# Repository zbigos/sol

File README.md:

# sol
high power LED lamp for workshop use

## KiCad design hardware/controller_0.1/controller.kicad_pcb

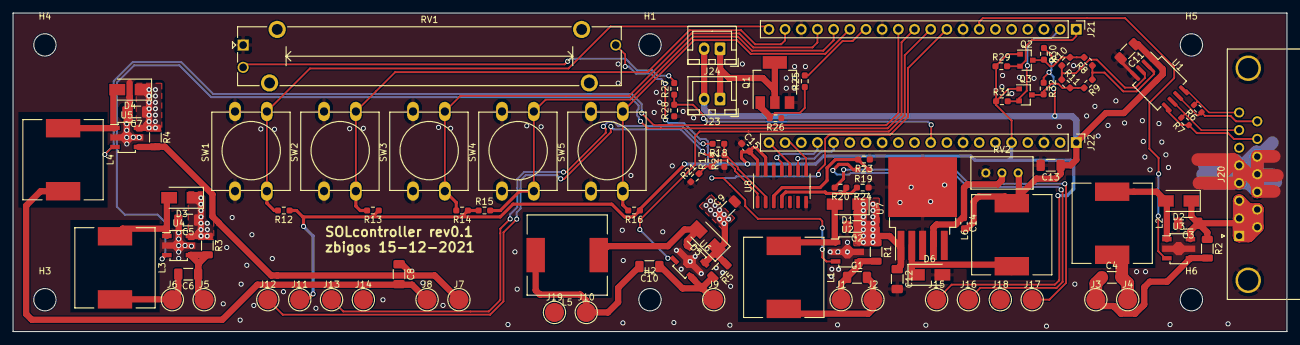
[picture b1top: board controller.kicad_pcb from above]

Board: 2 copper layers, 200.0 x 50.0 mm, 107 parts (0 on the bottom side), 58 nets.

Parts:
C1, C2, C3, C4, C5, C6, C7, C8, C9, C10, C11, C12, C13: C_Small; C_1206_3216Metric_Pad1.33x1.80mm_HandSolder
C14, C15: C_Small; C_0603_1608Metric_Pad1.08x0.95mm_HandSolder
D1, D2, D3, D4, D5, D6: D_Schottky; D_SMA
H1, H2, H3, H4, H5, H6: MountingHole; MountingHole_3.5mm
J1, J2, J3, J4, J5, J6, J7, J8, J9, J10, J11, J12, J13, J14, J15, J16, J17, J18, J19: Conn_01x01; TestPoint_Pad_D3.0mm
J20: DB15_Male_MountingHoles; DSUB-15_Male_Horizontal_P2.77x2.84mm_EdgePinOffset9.90mm_Ho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
J21, J22: Conn_01x20; PinHeader_1x20_P2.54mm_Vertical
J23, J24: Conn_01x02; JST_XH_B2B-XH-A_1x02_P2.50mm_Vertical
L1, L2, L3, L4, L5, L6: INDUCTOR; L_12x12mm_H8mm
Q1: Q_NMOS_GDS; SOT-223-3_TabPin2
Q2, Q3: BSS138; SOT-23
R1, R2, R3, R4, R5: R; R_1206_3216Metric
R6, R7: R_Small; R_0603_1608Metric
R8, R9, R10, R11, R12, R13, R14, R15, R16, R17, R18, R19, R20, R21, R22, R23, R24, R25, R26, R27, R28, R29, R30, R31, R32: R_Small; R_0603_1608Metric_Pad0.98x0.95mm_HandSolder
RV1: R_POT; Potentiometer_Bourns_PTA4543_Single_Slide
RV2: R_POT; Potentiometer_Bourns_3296W_Vertical
SW1, SW2, SW3, SW4, SW5: SW_Push; SW_PUSH-12mm
U1: MAX490E; SO-8_5.3x6.2mm_P1.27mm
U2, U3, U4, U5, U6: SCT2932F; SOT-89-5
U7: LM2596S-ADJ; TO-263-5_TabPin3
U8: MCP3204; SOIC-14_3.9x8.7mm_P1.27mm

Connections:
+5V: C11.1, C13.1, C14.2, J22.1, J23.2, J24.2, L6.2, R30.1, R32.1, RV2.1, U1.1 (VCC)
/3V3pico: C15.2, J11.1, J15.1, J22.5, Q2.1 (G), Q3.1 (G), R12.1, R13.1, R14.1, R15.1, R16.1, R29.1, R31.1, RV1.3, U8.13 (Vref), U8.14 (Vdd)
/B1: J21.20, R12.2, SW1.2
/B2: J21.19, R13.2, SW2.2
/B3: J21.17, R14.2, SW3.2
/B4: J21.16, R15.2, SW4.2
/B5: J21.15, R16.2, SW5.2
/CH1_CONTROL: J21.9, U2.3 (DIM)
/CH1_SINK: C1.2, J2.1, L1.2
/CH1_VSUP: C1.1, J1.1, R1.2, U2.4 (Isense)
/CH2_CONTROL: J21.7, U3.3 (DIM)
/CH2_SINK: C4.2, J4.1, L2.2
/CH2_VSUP: C4.1, J3.1, R2.2, U3.4 (Isense)
/CH3_CONTROL: J21.11, U4.3 (DIM)
/CH3_SINK: C6.2, J6.1, L3.2
/CH3_VSUP: C6.1, J5.1, R3.2, U4.4 (Isense)
/CH4_CONTROL: J21.12, U5.3 (DIM)
/CH4_SINK: C8.2, J8.1, L4.2
/CH4_VSUP: C8.1, J7.1, R4.2, U5.4 (Isense)
/CH5_CONTROL: J21.10, U6.3 (DIM)
/CH5_SINK: C10.2, J10.1, L5.2
/CH5_VSUP: C10.1, J9.1, R5.2, U6.4 (Isense)
/CLK: J22.17, U8.11 (CLK)
/FANCONTROL: J21.14, R25.2
/HRSRx: Q3.3 (D), R9.2, R11.2, R32.2
/HRSTx: Q2.3 (D), R8.2, R10.2, R30.2
/LEDRAIL: C2.1, C3.1, C5.1, C7.1, C9.1, C12.1, D1.1 (K), D2.1 (K), D3.1 (K), D4.1 (K), D5.1 (K), J20.1, J20.2, J20.3, J20.9, J20.10, R1.1, R2.1, R3.1, R4.1, R5.1, U2.5 (VIN), U3.5 (VIN), U4.5 (VIN), U5.5 (VIN), U6.5 (VIN), U7.1 (VIN)
/MISO: J22.20, U8.10 (Dout)
/MOSI: J22.16, U8.9 (Din)
/POT: J22.10, R27.1, R28.2
/RSRx: J21.2, Q3.2 (S), R31.2
/RSTx: J21.1, Q2.2 (S), R29.2
/TCHANNEL_1: J12.1, R17.2
/TCHANNEL_2: J13.1, R18.2
/TCHANNEL_3: J16.1, R19.2
/TCHANNEL_4: J17.1, R20.2
/nCS: J22.19, U8.8 (~CS~/SHDN)
GND: C2.2, C3.2, C5.2, C7.2, C9.2, C11.2, C12.2, C13.2, C15.1, D6.2 (A), J14.1, J18.1, J19.1, J20.0 (PAD), J20.4, J20.5, J20.11 (P111), J20.12, J20.13, J21.3, J21.8, J21.13, J21.18, J22.3, J22.8, J22.13, J22.18, Q1.3 (S), R21.1, R22.1, R23.1, R24.1, R26.1, R28.1, RV1.1, RV2.3, SW1.1, SW2.1, SW3.1, SW4.1, SW5.1, U1.4 (GND), U2.2 (GND), U3.2 (GND), U4.2 (GND), U5.2 (GND), U6.2 (GND), U7.3 (GND), U8.7 (DGND), U8.12 (AGND)
unnamed: C14.1, RV2.2, U7.4 (FB)
unnamed: D1.2 (A), L1.1, U2.1 (SW)
unnamed: D2.2 (A), L2.1, U3.1 (SW)
unnamed: D3.2 (A), L3.1, U4.1 (SW)
unnamed: D4.2 (A), L4.1, U5.1 (SW)
unnamed: D5.2 (A), L5.1, U6.1 (SW)
unnamed: D6.1 (K), L6.1, U7.2 (OUT)
unnamed: J20.7, R7.2, U1.6 (Z)
unnamed: J20.8, R6.2, U1.8 (A)
unnamed: J20.14, R7.1, U1.5 (Y)
unnamed: J20.15, R6.1, U1.7 (B)
unnamed: J23.1, J24.1, Q1.2 (D)
unnamed: Q1.1 (G), R25.1, R26.2
unnamed: R8.1, R9.1, U1.2 (RO)
unnamed: R10.1, R11.1, U1.3 (DI)
unnamed: R17.1, R21.2, U8.1 (CH0)
unnamed: R18.1, R22.2, U8.2 (CH1)
unnamed: R19.1, R23.2, U8.3 (CH2)
unnamed: R20.1, R24.2, U8.4 (CH3)
unnamed: R27.2, RV1.2

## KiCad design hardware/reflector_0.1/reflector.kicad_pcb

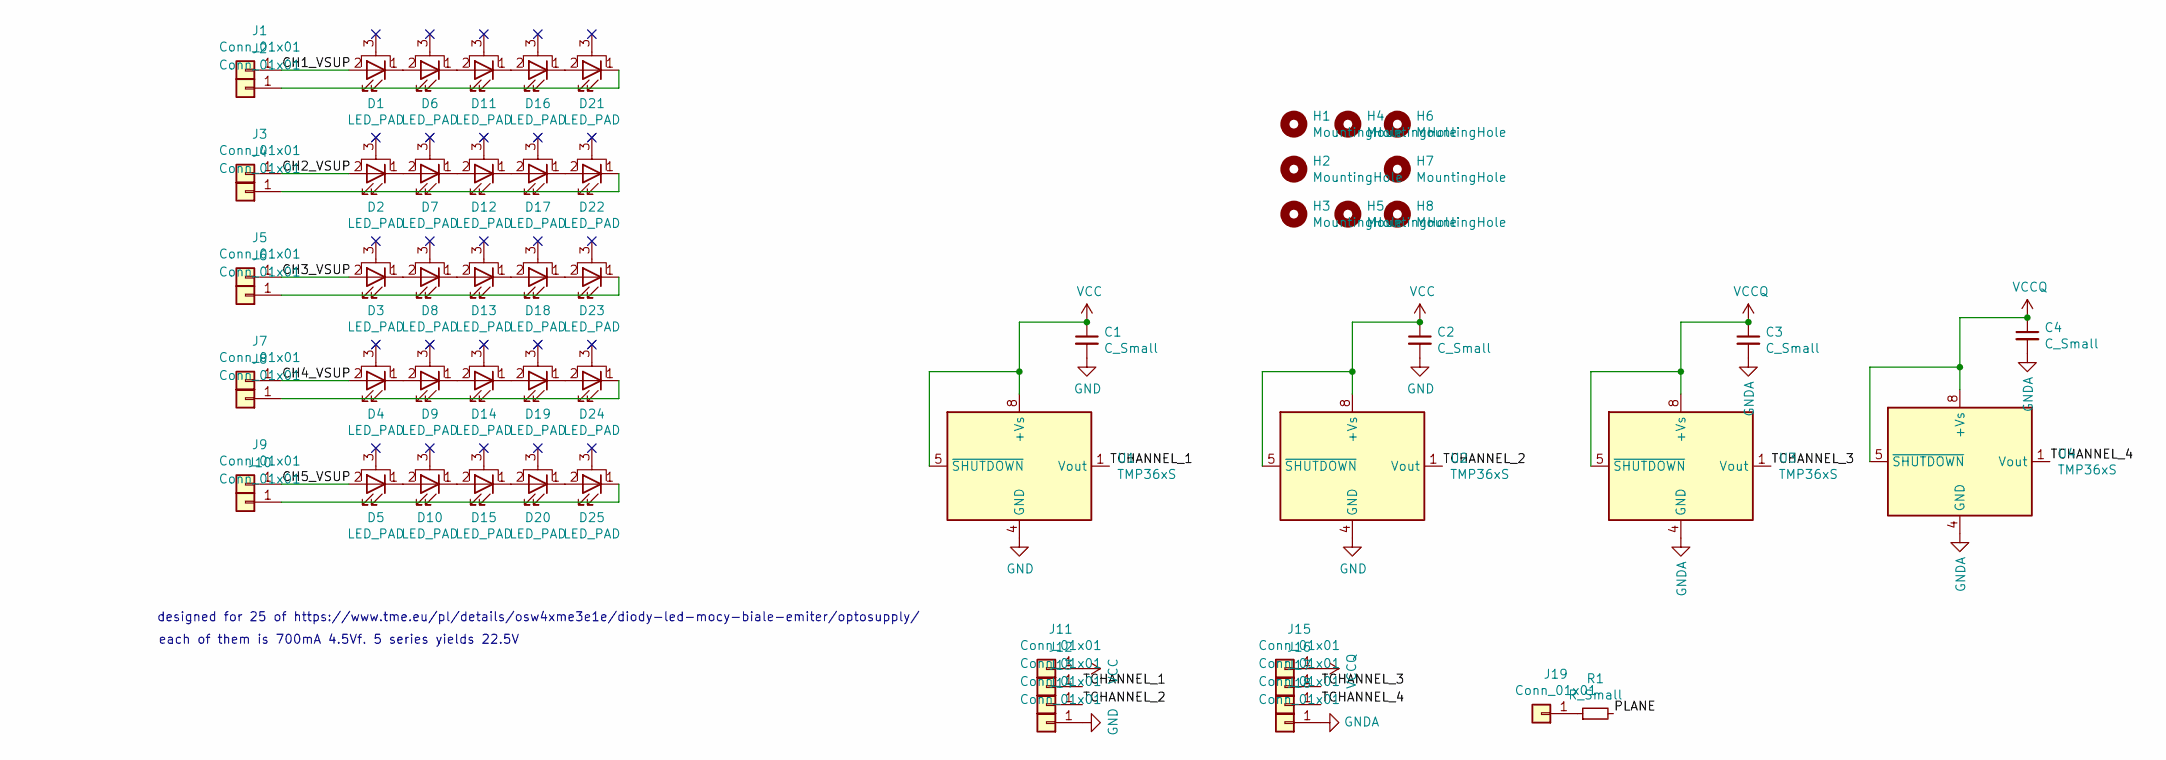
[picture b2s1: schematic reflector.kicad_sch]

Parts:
C1, C2, C3, C4: C_Small; C_1206_3216Metric_Pad1.33x1.80mm_HandSolder
D1, D2, D3, D4, D5, D6, D7, D8, D9, D10, D11, D12, D13, D14, D15, D16, D17, D18, D19, D20, D21, D22, D23, D24, D25: LED_PAD; LED_1W_3W_R8
H1, H2, H3, H4, H5, H6, H7, H8: MountingHole; MountingHole_3.5mm
J1, J2, J3, J4, J5, J6, J7, J8, J9, J10, J11, J12, J13, J14, J15, J16, J17, J18, J19: Conn_01x01; TestPoint_Pad_D3.0mm
R1: R_Small; R_0603_1608Metric_Pad0.98x0.95mm_HandSolder
U1, U2, U3, U4: TMP36xS; SOIC-8_3.9x4.9mm_P1.27mm

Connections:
/CH1_VSUP: D1.2 (A), J1.1
/CH2_VSUP: D2.2 (A), J3.1
/CH3_VSUP: D3.2 (A), J5.1
/CH4_VSUP: D4.2 (A), J7.1
/CH5_VSUP: D5.2 (A), J9.1
/PLANE: R1.2
/TCHANNEL_1: J12.1, U1.1 (Vout)
/TCHANNEL_2: J13.1, U2.1 (Vout)
/TCHANNEL_3: J16.1, U3.1 (Vout)
/TCHANNEL_4: J17.1, U4.1 (Vout)
GND: C1.2, C2.2, J14.1, U1.4 (GND), U2.4 (GND)
GNDA: C3.2, C4.2, J18.1, U3.4 (GND), U4.4 (GND)
unnamed: D1.1 (K), D6.2 (A)
unnamed: D2.1 (K), D7.2 (A)
unnamed: D3.1 (K), D8.2 (A)
unnamed: D4.1 (K), D9.2 (A)
unnamed: D10.1 (K), D15.2 (A)
unnamed: D5.1 (K), D10.2 (A)
unnamed: D11.1 (K), D16.2 (A)
unnamed: D6.1 (K), D11.2 (A)
unnamed: D12.1 (K), D17.2 (A)
unnamed: D7.1 (K), D12.2 (A)
unnamed: D13.1 (K), D18.2 (A)
unnamed: D8.1 (K), D13.2 (A)
unnamed: D14.1 (K), D19.2 (A)
unnamed: D9.1 (K), D14.2 (A)
unnamed: D15.1 (K), D20.2 (A)
unnamed: D16.1 (K), D21.2 (A)
unnamed: D17.1 (K), D22.2 (A)
unnamed: D18.1 (K), D23.2 (A)
unnamed: D19.1 (K), D24.2 (A)
unnamed: D20.1 (K), D25.2 (A)
unnamed: D21.1 (K), J2.1
unnamed: D22.1 (K), J4.1
unnamed: D23.1 (K), J6.1
unnamed: D24.1 (K), J8.1
unnamed: D25.1 (K), J10.1
unnamed: J19.1, R1.1
VCC: C1.1, C2.1, J11.1, U1.5 (~SHUTDOWN), U1.8 (+Vs), U2.5 (~SHUTDOWN), U2.8 (+Vs)
VCCQ: C3.1, C4.1, J15.1, U3.5 (~SHUTDOWN), U3.8 (+Vs), U4.5 (~SHUTDOWN), U4.8 (+Vs)
no_connect_41: D1.3 (PAD)
no_connect_42: D10.3 (PAD)
no_connect_43: D11.3 (PAD)
no_connect_44: D12.3 (PAD)
no_connect_45: D13.3 (PAD)
no_connect_46: D14.3 (PAD)
no_connect_47: D15.3 (PAD)
no_connect_48: D16.3 (PAD)
no_connect_49: D17.3 (PAD)
no_connect_50: D18.3 (PAD)
no_connect_51: D19.3 (PAD)
no_connect_52: D2.3 (PAD)
no_connect_53: D20.3 (PAD)
no_connect_54: D21.3 (PAD)
no_connect_55: D22.3 (PAD)
no_connect_56: D23.3 (PAD)
no_connect_57: D24.3 (PAD)
no_connect_58: D25.3 (PAD)
no_connect_59: D3.3 (PAD)
no_connect_60: D4.3 (PAD)
no_connect_61: D5.3 (PAD)
no_connect_62: D6.3 (PAD)
no_connect_63: D7.3 (PAD)
no_connect_64: D8.3 (PAD)
no_connect_65: D9.3 (PAD)

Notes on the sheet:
each of them is 700mA 4.5Vf. 5 series yields 22.5V
designed for 25 of https://www.tme.eu/pl/details/osw4xme3e1e/diody-led-mocy-biale-emiter/optosupply/

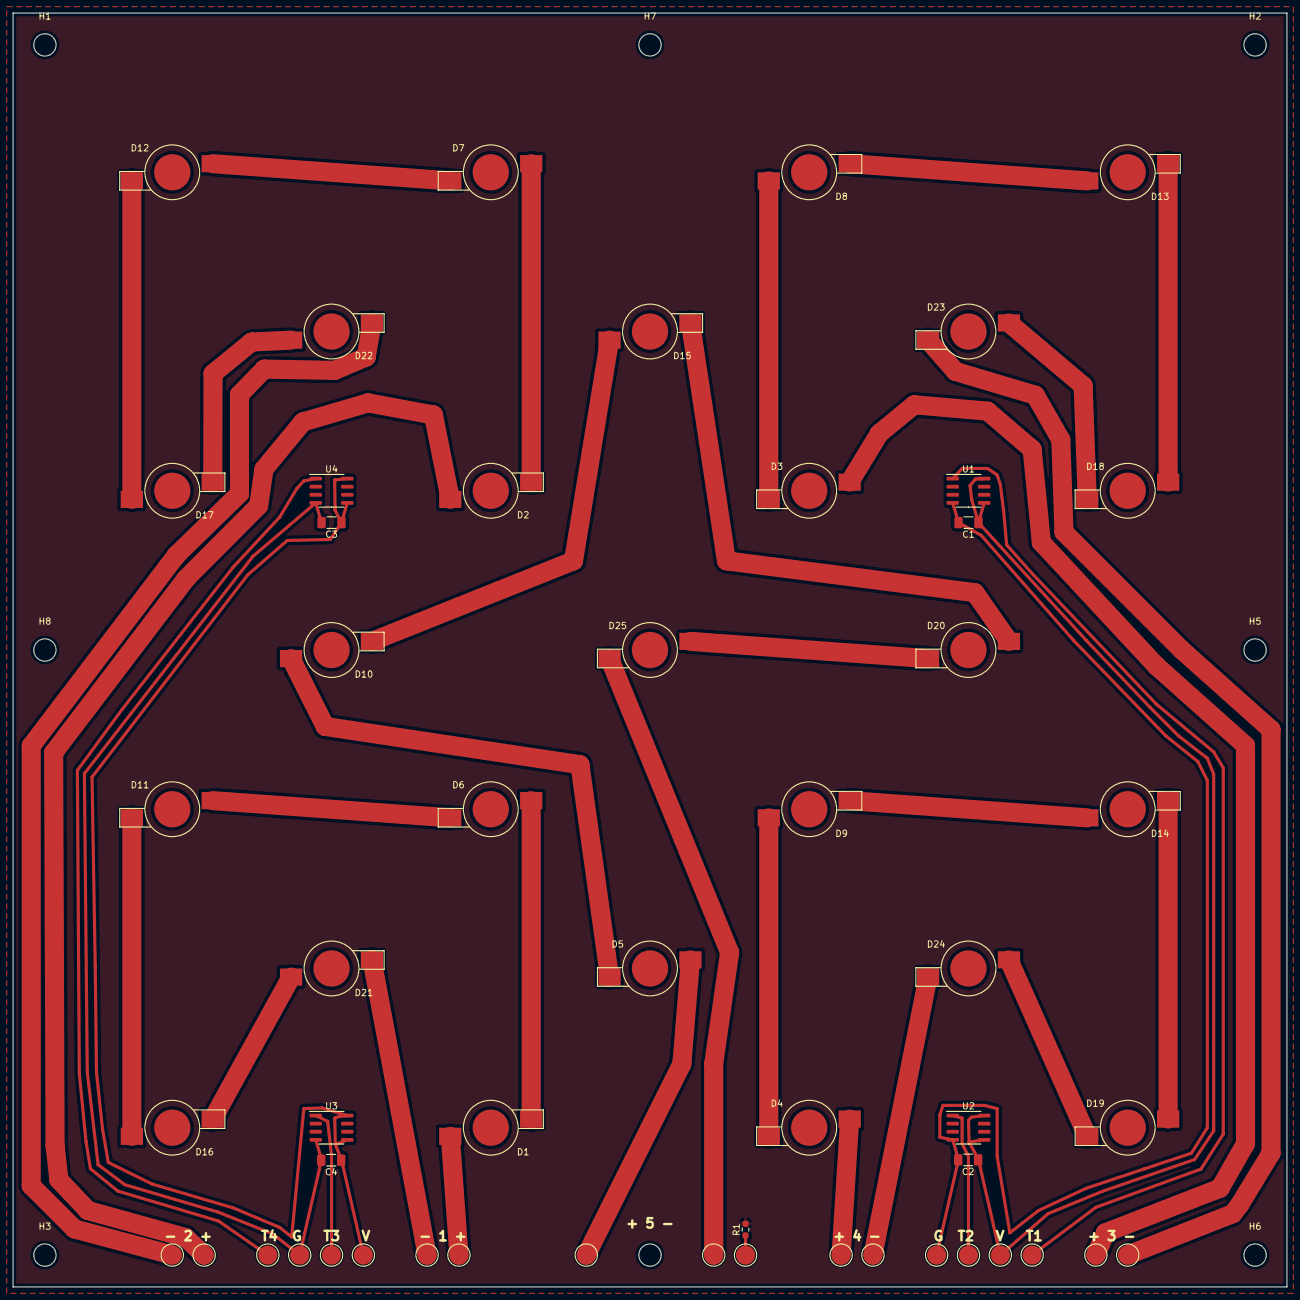
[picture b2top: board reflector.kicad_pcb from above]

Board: 2 copper layers, 200.0 x 200.0 mm, 61 parts (0 on the bottom side), 39 nets.

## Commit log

2021-12-10 reflector 0.1
2021-12-15 final
